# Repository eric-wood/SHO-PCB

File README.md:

# SHO Boost PCB

This is my first go at doing any sort of PCB work, so I picked a simple boost circuit: the Zvex SHO.  To make it more usable for my use-case, I included the master volume control mod you've probably seen elsewhere.

## Getting it made

For Oshpark you can upload the KiCad PCB file directly and it should Just Work. For other fabs grab the files in the `gerber` folder.

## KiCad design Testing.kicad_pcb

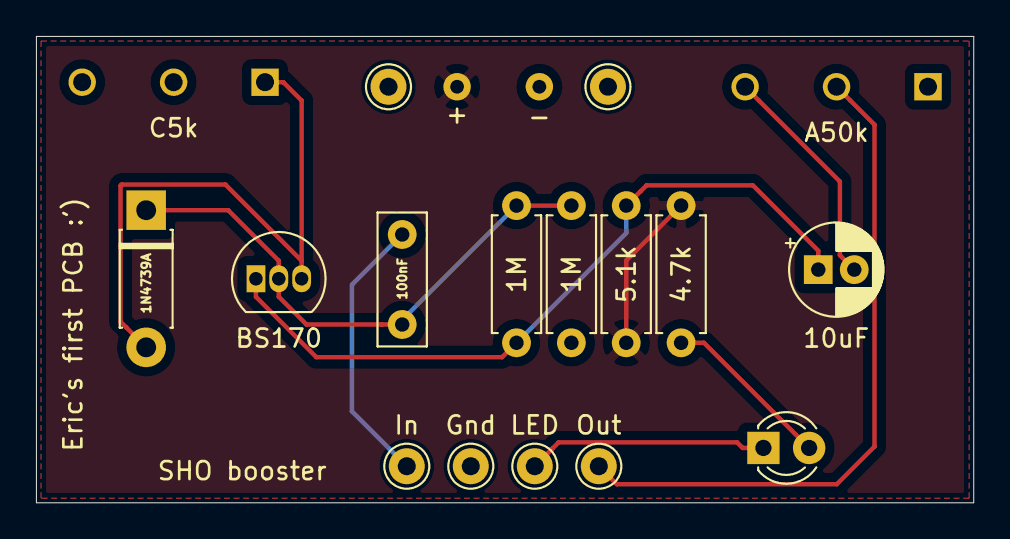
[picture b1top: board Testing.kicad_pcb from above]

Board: 2 copper layers, 52.1 x 25.9 mm, 18 parts (0 on the bottom side), 10 nets.

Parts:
1M, 1M#2: 1M; R_Axial_DIN0207_L6.3mm_D2.5mm_P7.62mm_Horizontal
1N4739A: 1N4739A; D_DO-41_SOD81_P7.62mm_Horizontal
4.7k: 4.7k; R_Axial_DIN0207_L6.3mm_D2.5mm_P7.62mm_Horizontal
5.1k: 5.1k; R_Axial_DIN0207_L6.3mm_D2.5mm_P7.62mm_Horizontal
10uF: 10uF; CP_Radial_D5.0mm_P2.00mm
100nF: 100nF; C_Rect_L7.2mm_W2.5mm_P5.00mm_FKS2_FKP2_MKS2_MKP2
A50k: A50k; Alpha Pot 9mm
BS170: BS170; TO-92_Inline
C5k: C5k; Alpha Pot 9mm
D2: LED; LED_D3.0mm
Gnd: Gnd; Pin_D1.0mm_L10.0mm
In: In; Pin_D1.0mm_L10.0mm
J4: Jack-DC; DC Power
J6: In Sleeve; Pin_D1.0mm_L10.0mm
J7: Out Sleeve; Pin_D1.0mm_L10.0mm
LED: LED; Pin_D1.0mm_L10.0mm
Out: Out; Pin_D1.0mm_L10.0mm

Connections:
+9V: 4.7k.2, 5.1k.1, J4.1
GND: 1M.2, A50k.1, C5k.2, Gnd.1, J4.2, J6.1, J7.1
unnamed: 1M.1, 1M#2.2, 1N4739A.1, 100nF.1, BS170.2
unnamed: 100nF.2, In.1
unnamed: 1M#2.1, 5.1k.2, 10uF.1, BS170.1
unnamed: 10uF.2, A50k.3
unnamed: 1N4739A.2, BS170.3, C5k.1
unnamed: D2.1, LED.1
unnamed: 4.7k.1, D2.2
unnamed: A50k.2, Out.1

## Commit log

2020-05-24 First run
2020-05-24 Gitignore
2020-05-24 Remove some junk
2020-05-24 Include gerber files
2020-05-24 cleaning, add README
2020-05-25 pcb layout: move some things around
    This mostly involved swapping the transistor with the output coupling
    capacitor so that the amplifier and feedback was on the left, and the
    output stages were on the right. I also rotated one resistor so the
    nets were closer to each other, and swapped a few of the traces to other
    layers of the PCB so that they could be shorter as well.
    Overall, the result is pretty much just shorter traces and beefier
2020-05-25 why does this fail DRC??
2020-05-25 Updated routing
2020-05-25 Remove vestigial trace
2020-05-25 one last update
2020-05-25 Rename everything, final silkscreen
2020-05-25 Final cleanup
